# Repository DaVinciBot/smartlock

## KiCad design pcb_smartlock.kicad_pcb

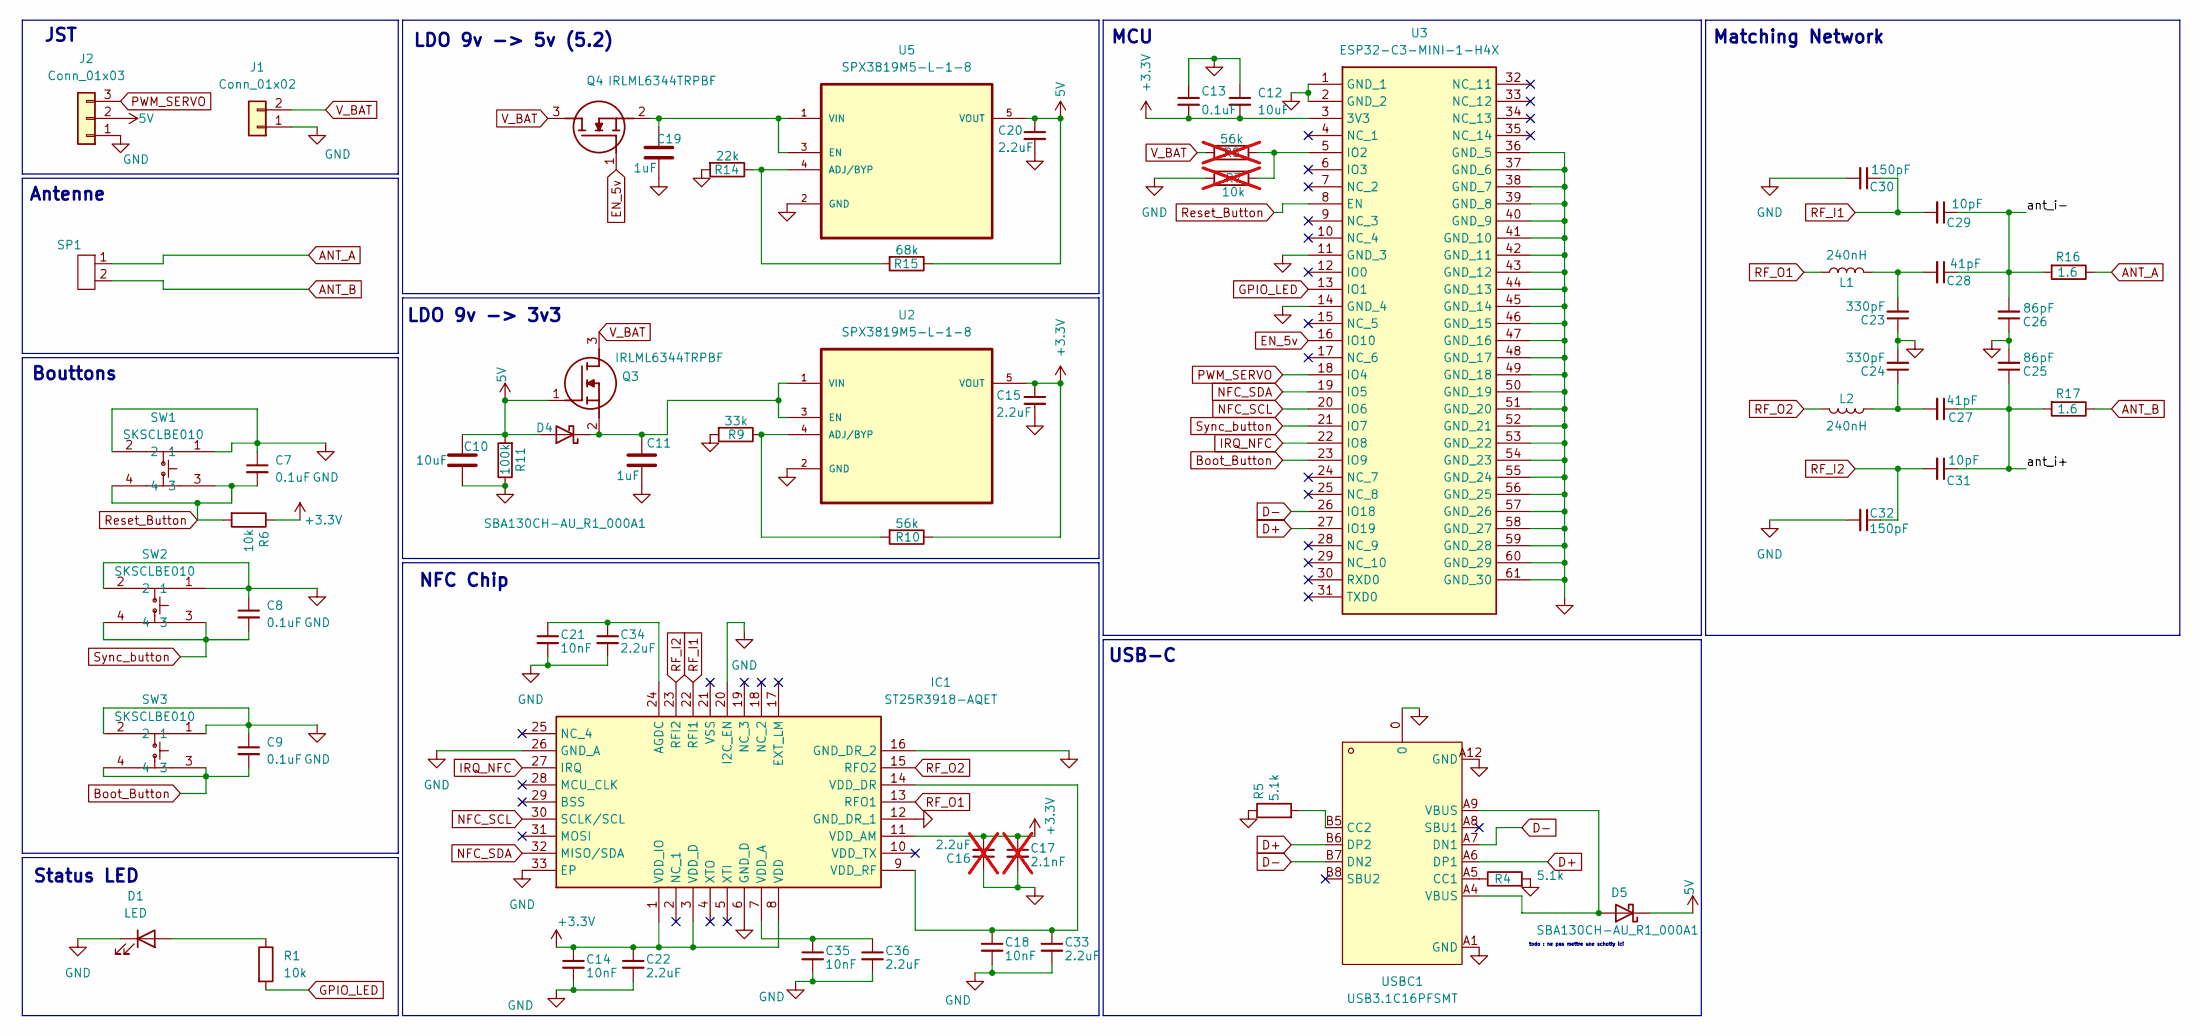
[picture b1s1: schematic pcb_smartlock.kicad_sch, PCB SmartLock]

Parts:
C7, C8, C13: 0.1uF; C_0603_1608Metric
C9: 0.1uF; C_0603_1608Metric_Pad1.08x0.95mm
C10, C12: 10uF; C_0603_1608Metric
C11, C19: 1uF; C_0603_1608Metric
C14, C18, C21, C35: 10nF; C_0603_1608Metric
C15, C20, C22, C33, C34, C36: 2.2uF; C_0603_1608Metric
C16: 2.2uF; C_0603_1608Metric; not fitted
C17: 2.1nF; C_0603_1608Metric; not fitted
C23, C24: 330pF; C_0603_1608Metric
C25, C26: 86pF; C_0603_1608Metric
C27, C28: 41pF; C_0603_1608Metric
C29, C31: 10pF; C_0603_1608Metric
C30, C32: 150pF; C_0603_1608Metric
D1: LED; LED_0603_1608Metric
D4, D5: SBA130CH-AU_R1_000A1; SOD-323HE
IC1: ST25R3918-AQET; QFN50P500X500X100-33N-D; Mouser Part Number 511-ST25R3918-AQET
J1: Conn_01x02; JST_PH_S2B-PH-K_1x02_P2.00mm_Horizontal
J2: Conn_01x03; PinHeader_1x03_P2.54mm_Vertical
L1, L2: 240nH; L_0603_1608Metric
Q3, Q4: IRLML6344TRPBF; SOT95P237X112-3N; Mouser Part Number 942-IRLML6344TRPBF
R1, R6: 10k; R_0603_1608Metric
R4, R5: 5.1k; R_0603_1608Metric
R7: 10k; R_0603_1608Metric; not fitted
R8: 56k; R_0603_1608Metric; not fitted
R9: 33k; R_0603_1608Metric
R10: 56k; R_0603_1608Metric
R11: 100k; R_0603_1608Metric
R14: 22k; R_0603_1608Metric
R15: 68k; R_0603_1608Metric
R16, R17: 1.6; R_0603_1608Metric
SP1: QFN-2_2x1_Pitch0.3mm
SW1, SW2, SW3: SKSCLBE010; KEY-SMD_4P-SKSCLXX010; LCSC Part C115361
U2, U5: SPX3819M5-L-1-8; SOT95P280X145-5N; MPN SPX3819M5-L-1-8
U3: ESP32-C3-MINI-1-H4X; ESP32C3MINI1H4X; Mouser Part Number 356-ESP32C3MINI1H4X
USBC1: USB3.1C16PFSMT; USB-C-SMD_TYPE-C-USB-17; LCSC Part C167321

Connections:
5V: C10.2, C20.1, D4.2 (A), D5.1 (K), J2.2, Q3.1 (G), R11.2, R15.1, U5.5 (VOUT)
+3.3V: C12.2, C13.2, C14.1, C15.1, C16.2, C17.1, C22.1, IC1.1 (VDD_IO), IC1.3 (VDD_D), IC1.8 (VDD), IC1.11 (VDD_AM), R6.1, R10.1, U2.5 (VOUT), U3.3 (3V3)
/ant_i+: C25.1, C27.1, C31.1, R17.2
/ant_i-: C26.2, C28.1, C29.1, R16.2
ANT_A: R16.1, SP1.1
ANT_B: R17.1, SP1.2
Boot_Button: C9.2, SW3.3, SW3.4, U3.23 (IO9)
D+: U3.27 (IO19), USBC1.A6 (DP1), USBC1.B6 (DP2)
D-: U3.26 (IO18), USBC1.A7 (DN1), USBC1.B7 (DN2)
EN_5v: Q4.1 (G), U3.16 (IO10)
GND: C7.1, C8.1, C9.1, C10.1, C11.1, C12.1, C13.1, C14.2, C15.2, C16.1, C17.2, C18.2, C19.1, C20.2, C21.2, C22.2, C23.1, C24.2, C25.2, C26.1, C30.2, C32.2, C33.2, C34.2, C35.2, C36.2, D1.1 (K), IC1.6 (GND_D), IC1.12 (GND_DR_1), IC1.16 (GND_DR_2), IC1.20 (I2C_EN), IC1.26 (GND_A), IC1.33 (EP), J1.1, J2.1, R4.2, R5.1, R7.2, R9.2, R11.1, R14.2, SW1.1, SW1.2, SW2.1, SW2.2, SW3.1, SW3.2, U2.2 (GND), U3.1 (GND_1), U3.2 (GND_2), U3.11 (GND_3), U3.14 (GND_4), U3.36 (GND_5), U3.37 (GND_6), U3.38 (GND_7), U3.39 (GND_8), U3.40 (GND_9), U3.41 (GND_10), U3.42 (GND_11), U3.43 (GND_12), U3.44 (GND_13), U3.45 (GND_14), U3.46 (GND_15), U3.47 (GND_16), U3.48 (GND_17), U3.49 (GND_18), U3.50 (GND_19), U3.51 (GND_20), U3.52 (GND_21), U3.53 (GND_22), U3.54 (GND_23), U3.55 (GND_24), U3.56 (GND_25), U3.57 (GND_26), U3.58 (GND_27), U3.59 (GND_28), U3.60 (GND_29), U3.61 (GND_30), U5.2 (GND), USBC1.0, USBC1.A1 (GND), USBC1.A12 (GND)
GPIO_LED: R1.2, U3.13 (IO1)
IRQ_NFC: IC1.27 (IRQ), U3.22 (IO8)
NFC_SCL: IC1.30 (SCLK/SCL), U3.20 (IO6)
NFC_SDA: IC1.32 (MISO/SDA), U3.19 (IO5)
unnamed: C23.2, C28.2, L1.2
unnamed: C24.1, C27.2, L2.1
unnamed: D1.2 (A), R1.1
unnamed: C11.2, D4.1 (K), Q3.2 (S), U2.1 (VIN), U2.3 (EN)
unnamed: D5.2 (A), USBC1.A4 (VBUS), USBC1.A9 (VBUS)
unnamed: C21.1, C34.1, IC1.24 (AGDC)
unnamed: C35.1, C36.1, IC1.7 (VDD_A)
unnamed: C18.1, C33.1, IC1.9 (VDD_RF), IC1.14 (VDD_DR)
unnamed: C19.2, Q4.2 (S), U5.1 (VIN), U5.3 (EN)
unnamed: R9.1, R10.2, U2.4 (ADJ/BYP)
unnamed: R7.1, R8.1, U3.5 (IO2)
unnamed: R14.1, R15.2, U5.4 (ADJ/BYP)
unnamed: R4.1, USBC1.A5 (CC1)
unnamed: R5.2, USBC1.B5 (CC2)
PWM_SERVO: J2.3, U3.18 (IO4)
RF_I1: C29.2, C30.1, IC1.22 (RFI1)
RF_I2: C31.2, C32.1, IC1.23 (RFI2)
RF_O1: IC1.13 (RFO1), L1.1
RF_O2: IC1.15 (RFO2), L2.2
Reset_Button: C7.2, R6.2, SW1.3, SW1.4, U3.8 (EN)
Sync_button: C8.2, SW2.3, SW2.4, U3.21 (IO7)
V_BAT: J1.2, Q3.3 (D), Q4.3 (D), R8.2

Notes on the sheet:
todo : ne pas mettre une schotty ici
Antenne
LDO 9v -> 5v (5.2)
USB-C
JST
Bouttons
LDO 9v -> 3v3
Status LED
NFC Chip
MCU
Matching Network

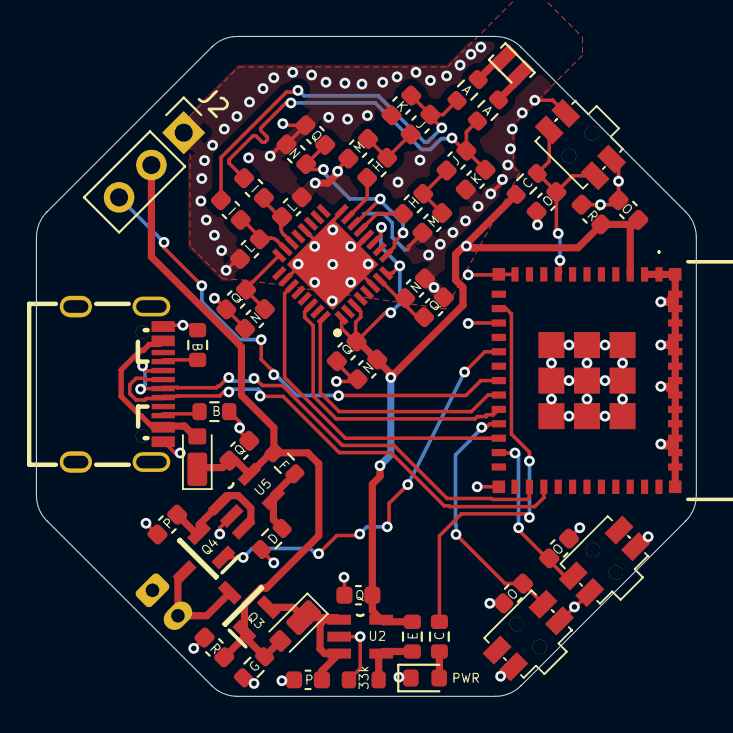
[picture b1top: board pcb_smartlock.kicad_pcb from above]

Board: 2 copper layers, 36.7 x 36.7 mm, 57 parts (1 on the bottom side), 36 nets.

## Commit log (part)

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2026-03-17 Alpha of the PCB
2026-03-17 Add Assets
2026-03-19 Finition PCB des boutons
    J'ai relié chacun des 3 boutons à leur source de tension et à un GND.
2026-06-28 Fix most of routing
    TODO : silkscreen
